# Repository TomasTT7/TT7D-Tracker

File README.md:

# TT7D-Tracker
This is the main repository for TT7D, a simple APRS / RTTY high altitude balloon tracker. It includes the board and schematic design files for Eagle, and the current firmware.

### Components:
- microcontroller: ATmega328P-AU
- GNSS module: u-blox MAX-M7 / MAX-M8 / GM10
- transmitter: Si4060 / Si4063 / Si4460 / Si4463
- TCXO: IT3205CE
- boost regulator: MCP1640B
- power supply: AAA battery / 2x solar cell
- GNSS antenna: JTI 1575AT43A0040 / wire

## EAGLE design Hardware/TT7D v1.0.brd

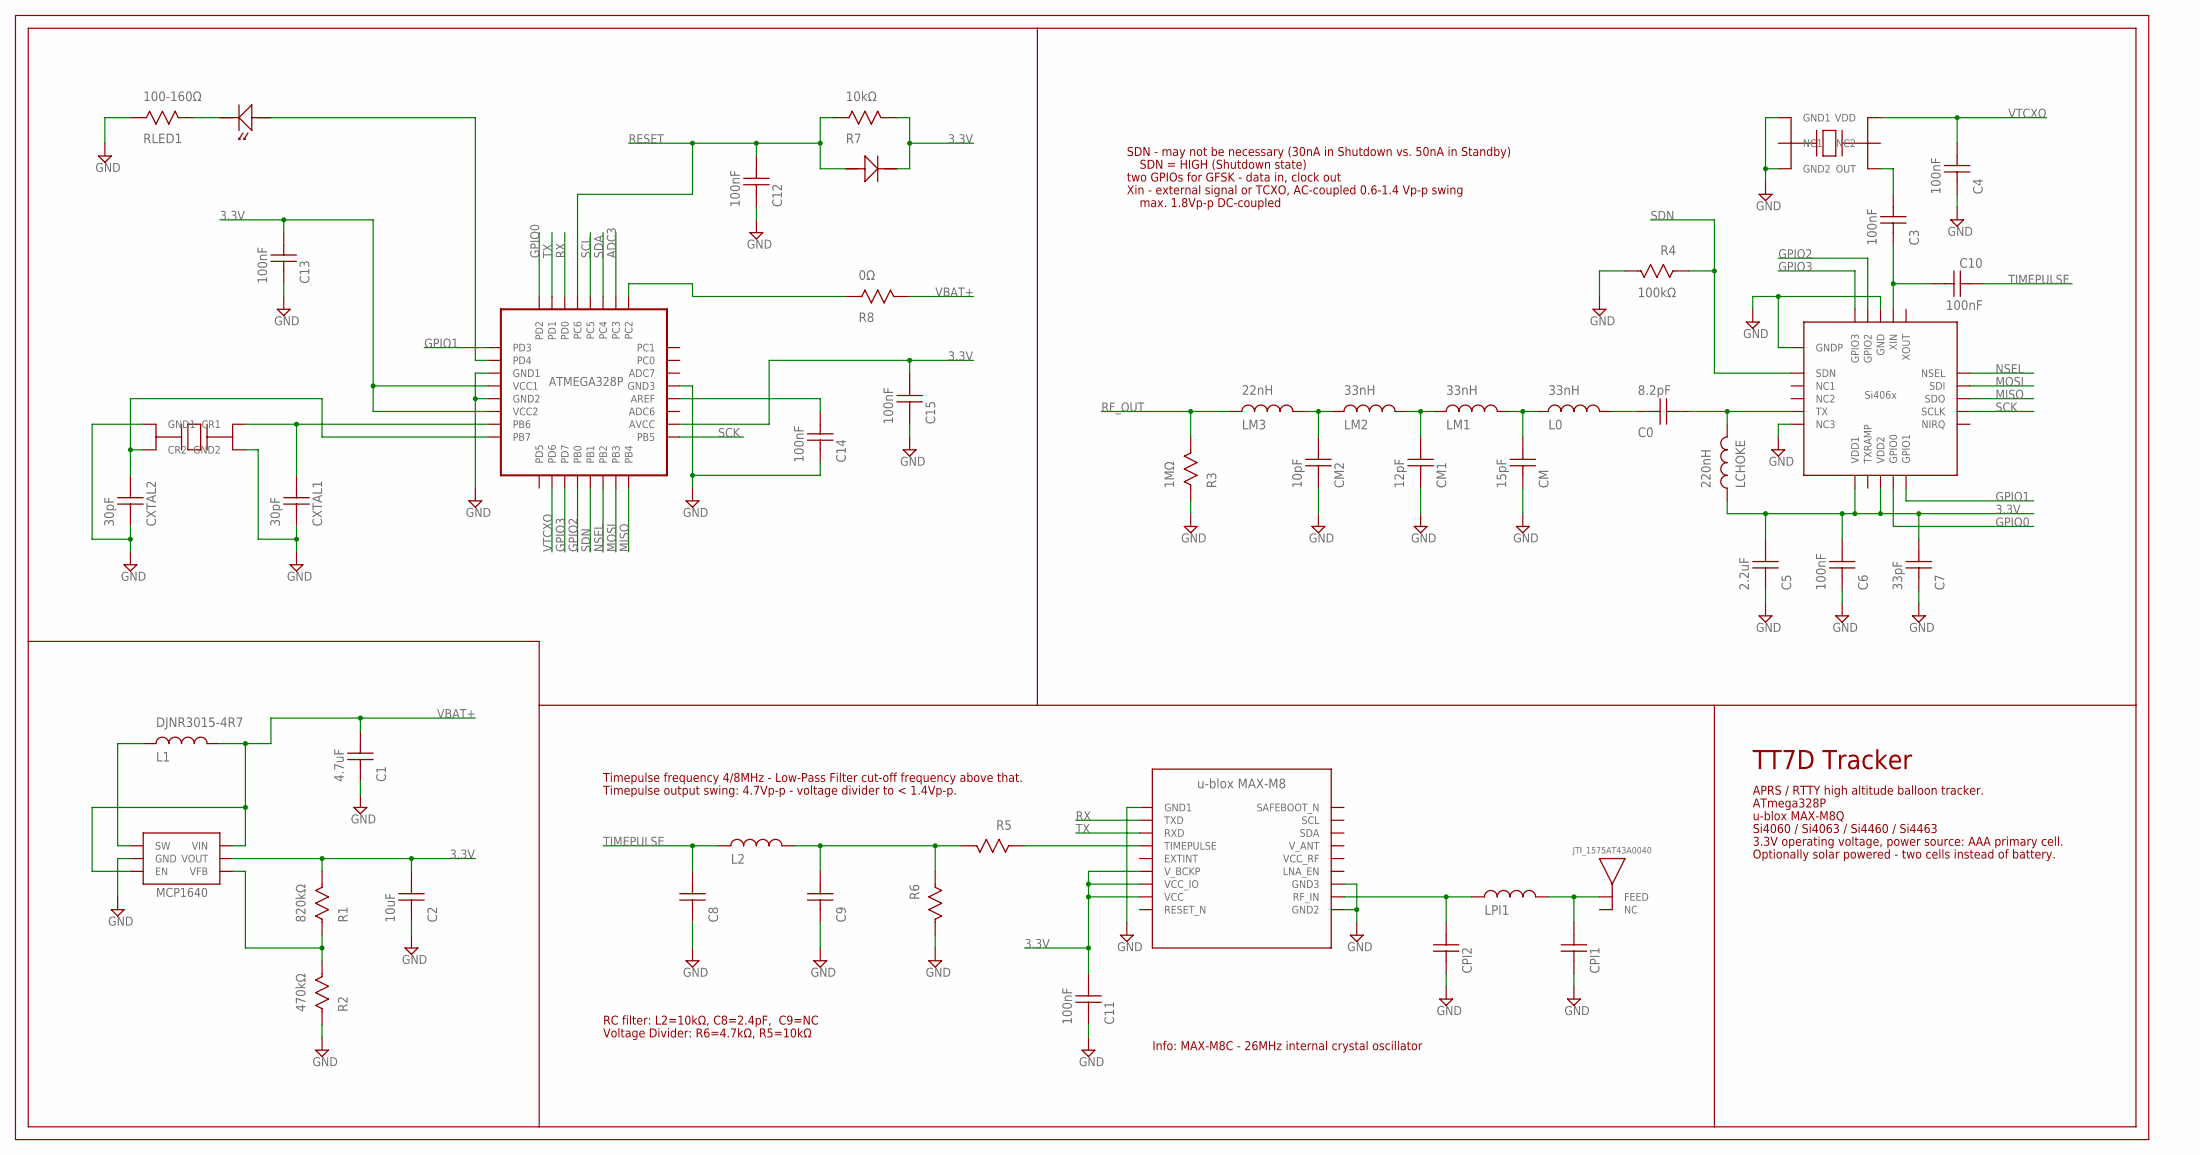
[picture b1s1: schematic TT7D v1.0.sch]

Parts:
ANT1: JTI_1575AT43A0040
C0: 8.2pF; CAP0402
C1: 4.7uF; CAP0402
C2: 10uF; CAP0402
C3, C4, C6, C10, C11, C12, C13, C14, C15: 100nF; CAP0402
C5: 2.2uF; CAP0402
C7: 33pF; CAP0402
C8, C9: CAP0402
CM: 15pF; CAP0402
CM1: 12pF; CAP0402
CM2: 10pF; CAP0402
CPI1, CPI2: CAP0402
CXTAL1, CXTAL2: 30pF; CAP0402
D1: DIODE0402
L0: 33nH; IND0402
L1: DJNR3015-4R7; DJNR3015
L2: IND0402
LCHOKE: 220nH; IND0402
LED1: LED0603
LM1, LM2: 33nH; IND0402
LM3: 22nH; IND0402
LPI1: IND0402
R1: 820kΩ; RES0402
R2: 470kΩ; RES0402
R3: 1MΩ; RES0402
R4: 100kΩ; RES0402
R5, R6: RES0402
R7: 10kΩ; RES0402
R8: 0Ω; RES0402
RLED1: 100-160Ω; RES0402
U1: ATMEGA328P-AU
U2: UBLOX_MAX-7C
U3: SI406X
U4: IT3205CE_TCXO_6P
U5: MCP1640
XTAL1: LFXTAL055663

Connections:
3.3V: C2.P$2, C5.P$2, C6.P$2, C7.P$2, C11.P$2, C13.P$2, C15.P$2, D1.CATHODE, LCHOKE.P$1, R1.P$2, R7.P$2, U1.AVCC, U1.VCC1, U1.VCC2, U2.VCC, U2.VCC_IO, U2.V_BCKP, U3.VDD1, U3.VDD2, U5.VOUT
ADC3: U1.PC3
GND: C1.P$1, C2.P$1, C4.P$1, C5.P$1, C6.P$1, C7.P$1, C8.P$1, C9.P$1, C11.P$1, C12.P$1, C13.P$1, C14.P$1, C15.P$1, CM.P$1, CM1.P$1, CM2.P$1, CPI1.P$1, CPI2.P$1, CXTAL1.P$1, CXTAL2.P$1, R2.P$1, R3.P$1, R4.P$2, R6.P$2, RLED1.P$1, U1.GND1, U1.GND2, U1.GND3, U2.GND1, U2.GND2, U2.GND3, U3.GND, U3.GNDP, U3.NC3, U4.GND1, U4.GND2, U5.GND, XTAL1.GND1, XTAL1.GND2
GPIO0: U1.PD2, U3.GPIO0
GPIO1: U1.PD3, U3.GPIO1
GPIO2: U1.PB0, U3.GPIO2
GPIO3: U1.PD7, U3.GPIO3
MISO: U1.PB4, U3.SDO
MOSI: U1.PB3, U3.SDI
unnamed: CXTAL2.P$2, U1.PB7, XTAL1.CRYSTAL2 (CR2)
unnamed: CXTAL1.P$2, U1.PB6, XTAL1.CRYSTAL1 (CR1)
unnamed: LED1.CATHODE, RLED1.P$2
unnamed: CPI2.P$2, LPI1.P$1, U2.RF_IN
unnamed: L1.P1, U5.SW
unnamed: CM.P$2, L0.P$1, LM1.P$2
unnamed: CM1.P$2, LM1.P$1, LM2.P$2
unnamed: R1.P$1, R2.P$2, U5.VFB
unnamed: CM2.P$2, LM2.P$1, LM3.P$2
unnamed: C0.P$1, L0.P$2
unnamed: C0.P$2, LCHOKE.P$2, U3.TX
unnamed: C14.P$2, U1.AREF
unnamed: C3.P$1, C10.P$2, U3.XIN
unnamed: C3.P$2, U4.OUT
unnamed: LED1.ANODE, U1.PD4
unnamed: R5.P$1, U2.TIMEPULSE
unnamed: C9.P$2, L2.P$2, R5.P$2, R6.P$1
unnamed: R8.P$1, U1.PC2
NSEL: U1.PB2, U3.NSEL
RESET: C12.P$2, D1.ANODE, R7.P$1, U1.PC6
RF_IN: ANT1.FEED, CPI1.P$2, LPI1.P$2
RF_OUT: LM3.P$1, R3.P$2
RX: U1.PD0, U2.TXD
SCK: U1.PB5, U3.SCLK
SCL: U1.PC5
SDA: U1.PC4
SDN: R4.P$1, U1.PB1, U3.SDN
TIMEPULSE: C8.P$2, C10.P$1, L2.P$1
TX: U1.PD1, U2.RXD
VBAT+: C1.P$2, L1.P2, R8.P$2, U5.EN, U5.VIN
VTCXO: C4.P$2, U1.PD6, U4.VDD

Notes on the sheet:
SDN - may not be necessary (30nA in Shutdown vs. 50nA in Standby)
SDN = HIGH (Shutdown state)
two GPIOs for GFSK - data in, clock out
Xin - external signal or TCXO, AC-coupled 0.6-1.4 Vp-p swing
max. 1.8Vp-p DC-coupled
Timepulse frequency 4/8MHz - Low-Pass Filter cut-off frequency above that.
Timepulse output swing: 4.7Vp-p - voltage divider to < 1.4Vp-p.
Info: MAX-M8C - 26MHz internal crystal oscillator
TT7D Tracker
APRS / RTTY high altitude balloon tracker.
ATmega328P
u-blox MAX-M8Q
Si4060 / Si4063 / Si4460 / Si4463
3.3V operating voltage, power source: AAA primary cell.
Optionally solar powered - two cells instead of battery.
RC filter: L2=10kΩ, C8=2.4pF, C9=NC
Voltage Divider: R6=4.7kΩ, R5=10kΩ

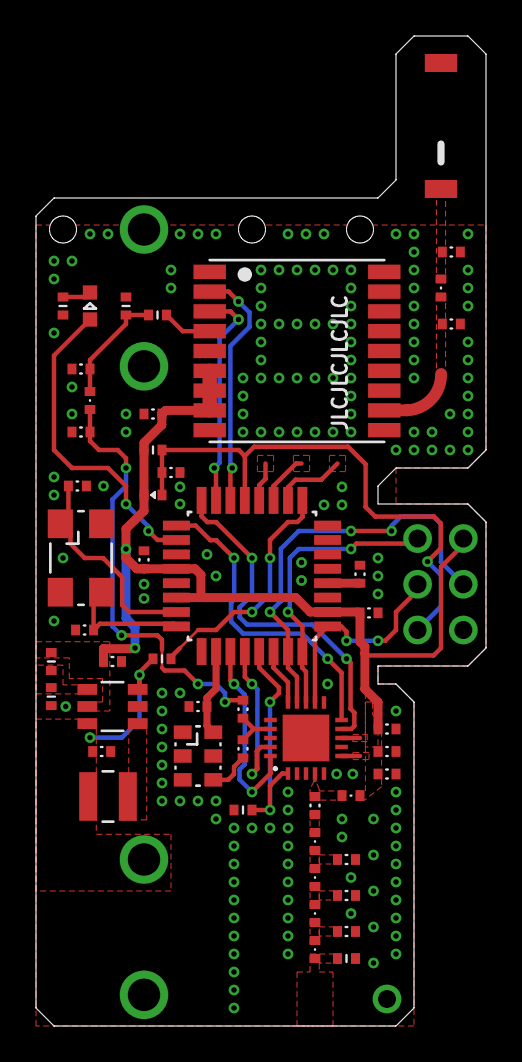
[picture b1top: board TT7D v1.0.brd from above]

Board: 2 copper layers, 25.0 x 55.0 mm, 49 parts (0 on the bottom side), 37 nets.

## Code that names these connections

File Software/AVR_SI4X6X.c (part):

/*
	Si4x6x <-> ATmega328P
		NSEL	PB2 (SS)
		SDI		PB3 (MOSI)
		SDO		PB4 (MISO)
		SCLK	PB5 (SCK)
		
		GPIO0	PD2 (INT0 - external interrupt)		CTS (output) - HIGH when able to receive
		GPIO1	PD3 (INT1 - external interrupt)		TX_DATA_CLK (output) - for use in TX Direct Synchronous Mode
		GPIO2	PB0									INPUT (input) - TXDATA for TX Direct Mode
		GPIO3	PD7									TRISTATE - input and output drivers disabled
		
		SDN		PB1 (LOW - IC active, HIGH - IC shutdown)
		VTCXO	PD6 (if used)
	
	Si4x6x Reference (Xin pin)
		Timepulse	needs setting up via the GNSS module
		TCXO		needs power via PD6
	
	A single high precision local oscillator (LO) is used for transmit mode. The LO is generated by an integrated VCO
	and ΔΣ Fractional-N PLL synthesizer. The synthesizer is designed to support configurable data rates from 100 bps
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	SPI_deassert_SS();
	SI4X6X_rx_CTS(rx_buffer, 1);
	
	/* Assumes Timepulse to Xin pin already enabled. */
	if(tcxo)
	{
		DDRD |= (1 << PORTD6);											// set PD6 to OUTPUT
		PORTD |= (1 << PORTD6);											// set PD6 HIGH
	}
	
	/* ATmega328P Pins Setup */
	DDRD &= ~((1 << PORTD2) | (1 << PORTD3) | (1 << PORTD7));			// set PD2, PD3 and PD7 to INPUT
	DDRB |= (1 << PORTB1) | (1 << PORTB0);								// set PB0 and PB1 to OUTPUT
	PORTB &= ~(1 << PORTB0);											// set PB0 (GPIO2 - TXDATA) LOW
	
	/* POWER_UP Sequence */
	PORTB |= (1 << PORTB1);												// set PB1 (SDN) HIGH
	_delay_ms(1);
	PORTB &= ~(1 << PORTB1);											// set PB1 (SDN) LOW
	_delay_ms(10);														// wait for POR to finish
	
	SPI_assert_SS();
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	SI4X6X_change_state(1);												// SLEEP/STANDBY
	
	/* ATmega328P Pins Deinit */
	PORTB &= ~(1 << PORTB0);											// set PB0 (GPIO2 - TXDATA) LOW
	DDRB &= ~(1 << PORTB0);												// set PB0 to INPUT
	
	/* Deinit SDN */
	PORTB &= ~(1 << PORTB1);											// set PB1 (SDN) LOW
	DDRB &= ~(1 << PORTB1);												// set PB1 to INPUT
	
	/* TCXO Reference */
	if(tcxo)
	{
		PORTD &= ~(1 << PORTD6);										// set PD6 LOW
		DDRD &= ~(1 << PORTD6);											// set PD6 to INPUT
	}
}

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	CLEAR TO SEND (CTS)
		Checking CTS is used to make sure the internal MCU has executed the command and prepared the data to be output over the SDO pin.
	
	Function waits for the CTS signal on a GPIO0 pin.
*/
void SI4X6X_check_CTS(void)
{
	/* Assumes GPIO0 already configured to output CTS signal */
	
	uint32_t timeout = 15000;
	
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
/*
	TYPICAL SETTINGS
		GPIO0			8		disable pull-up, Clear To Send signal output
		GPIO1			16		disable pull-up, TX Data Clock signal output
		GPIO2			4		disable pull-up, TXDATA input for TX Direct Mode
		GPIO3			1		disable pull-up, Input and output drivers disabled
		NIRQ			0		disable pull-up, behavior of this pin is not modified
		SDO				0		disable pull-up, behavior of this pin is not modified
		GEN_CONFIG		0		GPIOs configured as outputs will have the highest drive strength
*/
void SI4X6X_setup_pins(uint8_t gpio0, uint8_t gpio1, uint8_t gpio2, uint8_t gpio3, uint8_t nirq, uint8_t sdo)
{
	uint8_t rx_buffer[16];
	
	SPI_assert_SS();
	SPI_master_transmit(0x13);											// GPIO_PIN_CFG
	SPI_master_transmit(gpio0);											// GPIO0
	SPI_master_transmit(gpio1);											// GPIO1
	SPI_master_transmit(gpio2);											// GPIO2
	SPI_master_transmit(gpio3);											// GPIO3
	SPI_master_transmit(nirq);											// NIRQ
	SPI_master_transmit(sdo);											// SDO
	SPI_master_transmit(0x00);											// Drive Strength
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		4					850-1050MHz
	
	REF_FREQ
		Frequency of the external signal at Xin pin - Timepulse / TCXO.
*/
void SI4X6X_set_frequency(uint32_t frequency, uint32_t ref_freq)
{
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	SPI_master_transmit(0x20);											// MODEM (group)
	SPI_master_transmit(0x01);											// 1 (num_props)
	SPI_master_transmit(0x00);											// MODEM_MOD_TYPE (start_prop)
	SPI_master_transmit(((async << 7) | (1 << 6) | (1 << 3) | mod));	// data (GPIO2 as the source of data, TX Direct Mode)
	SPI_deassert_SS();
	SI4X6X_rx_CTS(rx_buffer, 1);
}
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		uint8_t c = packet[i];
		
		/* Start Bit */
		PORTB &= ~(1 << PORTB0);										// set PB0 (GPIO2 - TXDATA) LOW
		while(!TC1_compare_match());
		
		/* Data Bits */
		for(uint8_t b = 0; b < 8; b++)
		{
			if(c & 0x01) PORTB |= (1 << PORTB0);						// set PB0 (GPIO2 - TXDATA) HIGH
			else PORTB &= ~(1 << PORTB0);								// set PB0 (GPIO2 - TXDATA) LOW
		
			c >>= 1;
			
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		}
		
		/* Stop Bits */
		PORTB |= (1 << PORTB0);											// set PB0 (GPIO2 - TXDATA) HIGH
		while(!TC1_compare_match());
		PORTB |= (1 << PORTB0);											// set PB0 (GPIO2 - TXDATA) HIGH
		while(!TC1_compare_match());
		
		WDT_timer_reset();												// Watchdog reset
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

/*
	External interrupt handler for PD3 - TX_DATA_CLK.
*/
ISR(INT1_vect)
{
	if(gfsk_toggle)
	{
		PORTB |= (1 << PORTB0);											// set PB0 (GPIO2 - TXDATA) HIGH
		gfsk_toggle = 0;
	}else{
		PORTB &= ~(1 << PORTB0);										// set PB0 (GPIO2 - TXDATA) LOW
		gfsk_toggle = 1;
	}
}
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
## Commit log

2019-11-25 Create temp
